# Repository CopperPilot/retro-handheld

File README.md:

# CopperPilot Retro Handheld

**A vertical pocket game console, 63 x 81 x 17 mm, in a CNC-machined metal case: STM32F412 microcontroller, 2.4-inch 320x240 IPS screen, D-pad, ABXY, Start/Select and four shoulder buttons, a 1200 mAh LiPo and USB-C charging. Designed end to end by CopperPilot from four photos and a two-line prompt.**

> [!NOTE]
> **Designed by [CopperPilot](https://copperpilot.ai).** CopperPilot's agents designed every board, schematic, layout and enclosure part in this repo from one prompt and a few reference photos, then checked them with the gates and reviews below. Nobody edited the design files by hand. The whole prompt was two lines ("Build me a handheld retro game console like the one in these photos. It should run simple 2D games and charge over USB-C."); the agents chose the parts, drew and routed the board, modelled the case and fixed every review finding themselves. **It has not been fabricated, assembled or powered on yet.** Everything here is open for review: if you see something a senior engineer would flag, [open an issue](../../issues/new/choose).

One two-layer board fills the case behind the screen. It carries the STM32F412 microcontroller, the button matrix
(surface-mount tact switches under the D-pad, face and shoulder buttons), the display's 18-pin ZIF connector, the
USB-C port and the battery charger. The LiPo pack sits behind the board; the CNC case is a front and a rear shell
with machined button caps and a display window.

## Status

### Done

- [x] Schematic: KiCad ERC, 0 errors
- [x] Layout: KiCad DRC with schematic parity and zone refill, 0 errors, 0 unconnected
- [x] Board rules no looser than the fab's limits, nothing silenced
- [x] Every part on the footprint and 3D model of its exact LCSC part
- [x] Every placed part has a live, in-stock LCSC/JLCPCB part number
- [x] High-speed groups (USB, MIPI, DDR where present) routed, length-matched, on target impedance
- [x] Every user-facing connector opens towards its case opening (checked on its 3D model)
- [x] Every connector mates from a known side, with a keep-clear zone KiCad DRC enforces
- [x] Both ends of every board-to-board cable carry the same signal on each wire
- [x] Datasheet-level design review: 0 P0 and 0 P1 findings open on every board
- [x] Enclosure parts are closed solids that fit the product envelope
- [x] Every enclosure part is manufacturable by its process (wall thickness, build size)
- [x] Full assembly with the real PCBAs: no collisions, seated or along any insertion path
- [x] Every cable joins two real connectors and fits its route in every pose
- [x] Every connector faces what mates with it; every screw hole sits on a boss
- [x] Every port opening has its connector right behind it
- [x] Every button and control physically reaches the switch it works
- [x] Every part is held by something real (screw, snap, clip, adhesive, press fit)
- [x] Gerbers, drill, BOM and CPL exist and agree with the PCB
- [x] Independent judge (compares renders to the reference photos): **9/10** ([notes](reviews/judge.md))

### Pending

- [ ] Gate `sourcing.bom` warn: 18 extended parts (each adds a JLCPCB feeder fee); prefer basic parts where equivalent
- [ ] Gate `kicad.drc` warn: DRC warning silk_over_copper x84
- [ ] **Not built.** The board has not been fabricated or assembled and the case has not been machined.
- [ ] **No firmware.** The game runtime, display driver, button scanning and battery monitoring for the STM32 are not written or tested.
- [ ] **Bought parts are specified from drawings.** The display module and the battery pack are modelled from their published drawings; the exact supplier parts still have to be confirmed against those models.
- [ ] **Thermal and battery life not measured.** No runtime estimate has been checked on hardware.

0 P0 · 0 P1 · 0 P2 review findings open; the full reviews with evidence and suggested fixes are in [reviews/](reviews). Every P0 and P1 the reviews raised was fixed before release.

## Build film

[docs/build-film.mp4](docs/build-film.mp4) (48 s, 720p). Every part backs out along the direction it was fitted and goes back in assembly order, and every cable is drawn along its real route. Every frame is replayed against the 3D models (no part passes through another, the camera stays outside, the product stays in frame and faces you, no flicker), and a separate critic watches the film ([notes](reviews/film.md)).

## Renders

| | |
|:---:|:---:|
| <br>*Three-quarter view* | <br>*Front* |
| <br>*Rear* | <br>*Exploded* |
| <br>*Inside, top cover lifted away, every cable* | <br>*Inside from below, bottom cover lifted away* |
| <br>*Ports* | <br>*Buttons and controls, next to the parts they press* |

## What's inside

**Power path:** USB-C (5 V, ESD-protected) → TP4056 linear charger → 1S 1200 mAh LiPo (pack with its own protection
board) → P-FET/Schottky power path → RT6150 buck-boost to a steady 3.3 V across the whole battery range.
**Display:** 2.4-inch 320x240 IPS module (ILI9341 class) over SPI on a 0.5 mm FPC, backlight switched by a MOSFET.

| Board | Size | Layers | Parts | Tracks | Vias | KiCad project | Review |
|---|---|---|---|---|---|---|---|
| Main board | 58 × 76 mm | 2 | 140 | 3,190 | 241 | [`hardware/pocket-retro-handheld.kicad_pro`](hardware/pocket-retro-handheld.kicad_pro) | [0 P0 · 0 P1](reviews/review-main.md) |

**Bought parts** (modelled from their drawings; the assembly checks use these models):

- **Display**: 2.4-inch 4:3 320x240 IPS TFT LCD module
- **Battery**: 1S 3.7V 1200mAh 503450 Li-Polymer rechargeable battery pack with built-in PCM protection and 2-pin 1.25mm Molex PicoBlade lead

## How it was made

CopperPilot's agents worked from the prompt in [reference/prompt.md](reference/prompt.md) and 4 reference photos ([reference/](reference)). The pipeline scopes the product into a written contract ([design/spec.yaml](design/spec.yaml)), designs the boards and the enclosure in parallel, integrates them, and only moves on when the gates pass. A separate review agent reads every board against the part datasheets, and a separate judge compares the result with the photos.

- Pipeline wall clock: about **19 h** over 9 launches (pipeline v98 to v127).

**Reference vs build:**

<sub>Reference photos of a commercial product, used here only for comparison. All rights belong to their owners; this project is not affiliated with or endorsed by the product's maker.</sub>

## Repository layout

```
hardware/          KiCad 10 projects (main board at the top, daughter boards in their own folders)
  lcsc.*, rea_refs.*   symbols, footprints and 3D models for every part, so the project opens anywhere
case/out/          enclosure parts (STL)
case/purchased/    bought parts used in the assembly checks
case/generate_case.py  the parametric enclosure source (uses CopperPilot's CAD helpers, not yet public)
fab/               Gerbers, drill, BOM, CPL, schematic PDF and STEP for each board; fab/mech/ enclosure STEP/STL
design/spec.yaml   the design contract the agents wrote and the gates check
reviews/           gate report, design reviews, the judge's notes, KiCad ERC/DRC
reference/         the prompt and the reference photos
docs/              build film and renders
```

## Manufacture

Every board targets **JLCPCB** standard PCB + assembly (1.6 mm FR-4); every part has an LCSC number. Per board: upload `*-gerbers.zip`, then `*-bom.csv` and `*-cpl.csv` for assembly, and check the part rotations in JLCPCB's preview before ordering.

The case (`fab/mech/`) is designed for CNC-machined 6061 aluminium (anodised); STEP files are included for machining
quotes and STLs for test prints.

> [!WARNING]
> This design has not been built yet. Fix or accept the open review findings above before you order boards, and expect a first revision to need changes.

## Review this design

Hardware gets better with more eyes on it. We'd like to hear what you'd flag:

- **Open an issue** ([design review template](../../issues/new/choose)) for a wrong pin, a missing part, a tight clearance, a part you'd swap, or a P1 above you disagree with.
- **Send a pull request** with a fix. Say which board and which reference designators it touches.
- **Build one** and tell us how it went: photos, bring-up notes and failures are all welcome.

Start with [reviews/](reviews): every finding has its evidence and a suggested fix.

## License

[CERN-OHL-S-2.0](LICENSE). You may use, study, modify, make and sell products from this design; modified versions must be shared under the same licence.

Part and product names are used only to say what fits; all trademarks belong to their owners.

<p align="center"><a href="https://copperpilot.ai"><b>Designed by CopperPilot</b></a>: we accelerate hardware design.<br><sub>More open designs: <a href="https://github.com/CopperPilot">github.com/CopperPilot</a></sub></p>

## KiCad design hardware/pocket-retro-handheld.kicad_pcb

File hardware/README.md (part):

# Pocket Retro Game Console — Hardware Design & Verification

Generated from `rea/spec.yaml` and completed with verified JLCPCB/LCSC components (`hardware/lcsc.kicad_sym`, `hardware/lcsc.pretty`, `hardware/lcsc.3dshapes`).

## 1. Architecture & Block Summary
- **MCU, Clock, VCAP_1 & VDDA Conditioning, External Button-Chord DFU Override, Bootloader Idle Conditioning & SWD Breakout (`U1`, `Y1`, `C1`, `C2`, `C10`, `L2`, `C21`, `C22`, `Q12`, `Q13`, `Q14`, `SW15`, `SW16`, `R25..R29`, `TP1..TP6`):**
  - `STM32F412RET6` (`U1`, LCSC `C89374`, LQFP-64): 100 MHz ARM Cortex-M4F (operated at `SYSCLK = 80 MHz` / `APB2 = 80 MHz`) with 512 KB Flash and 256 KB contiguous DMA-capable SRAM.
  - 12 MHz Low-$C_L$, Low-ESR HSE Crystal (`Y1`, `TXM12M0004322CBCDO00T`, LCSC `C362368`, SMD3225-4P): $C_L = 9\text{ pF}$, $\text{ESR}_{\max} = 60\ \Omega$, $C_0 \approx 3\text{ pF}$. Critical transconductance $g_{m,\text{crit}} = 4 \times 60\ \Omega \times (2\pi \times 12\text{ MHz})^2 \times (9\text{ pF} + 3\text{ pF})^2 \approx 0.20\text{–}0.25\text{ mA/V} \ll G_{m,\text{crit,max}} = 1.0\text{ mA/V}$ (gain margin $> 16$, compliant with ST AN2867 and STM32F412xE DS11189 Section 6.3.9). Load capacitors `C1 = C2 = 12 pF` 50 V C0G (`0402CG120J500NT`, LCSC `C1547`) provide $C_{L,\text{actual}} = (12 \times 12)/(12 + 12) + C_{\text{stray}}(3\text{ pF}) = 6\text{ pF} + 3\text{ pF} = 9.0\text{ pF}$.
  - Single-`VCAP_1` Core LDO Decoupling (`U1.30`): Because LQFP-64 bonds out a single internal core voltage regulator capacitor pin (`VCAP_1`, `U1.30`), `VCAP_1` is decoupled by a 4.7 uF 16 V 0603 X5R low-ESR ($\ll 1\ \Omega$) ceramic capacitor `C10` (`CL10A475KO8NNNC`, LCSC `C19666`), meeting ST DS11189 Table 21 and AN4488 ($1 \times 4.7\ \mu\text{F}$ nominal for single-VCAP packages).
  - Analog Supply Isolation (`U1.13` `VDDA/VREF+`): Isolated from digital `+3V3` via 0603 ferrite bead `L2` (`BLM18PG121SN1D`, LCSC `C14709`, $120\ \Omega$ @ 100 MHz, $R_{\text{DC}} = 50\text{ m}\Omega$, 2 A) feeding net `VDDA`, locally decoupled adjacent to `U1.13` (`VDDA`) and `U1.12` (`VSSA`) by `C21` = 100 nF (`CL05B104KB54PNC`, LCSC `C307331`) and `C22` = 1 uF (`CL05A105KO5NNNC`, LCSC `C29266`).
  - Factory-ROM USB DFU, External Button-Chord Recovery (`Select + R2 + B`), Reset & SWD Programming:
    - `BOOT0` (`U1.60`) has a 10 kOhm pull-down to `GND` (`R8`, LCSC `C25744`) for normal Flash boot (`BOOT1`/`PB2` pulled low via 10 kOhm `R11`).
    - For bare-PCBA bring-up prior to LCD installation, tactile switch `SW15` (`B3U-1000P`, LCSC `C231329`) and test pad `TP6` pull `BOOT0` to `+3V3`, tactile switch `SW16` (`B3U-1000P`) and `TP3` pull `NRST` (`U1.7`, with 10 kOhm pull-up `R7` and 100 nF filter `C8`) low, and `TP1..TP6` (`RH-5015`, LCSC `C5199798`) expose `SWDIO` (`PA13`), `SWCLK` (`PA14`), `NRST`, `+3V3`, `GND`, and `BOOT0`.
    - For sealed-enclosure recovery without opening the press-fit CNC shell, series P-MOSFETs `Q12` (`AO3401A`, Source on `+3V3`, Gate on `BTN_SELECT`, Drain on `BOOT0_CHORD_MID`) and `Q13` (`AO3401A`, Source on `BOOT0_CHORD_MID`, Gate on `BTN_R2`, Drain on `BOOT0`) pull `BOOT0` to `+3V3` (`3.30 V` across `R8 = 10 kOhm`) whenever external buttons `Select` (`SW9`) and `R2` (`SW13`) are held simultaneously. While `BOOT0 = 3.30 V` biases the gate of N-MOSFET `Q14` (`AO3400A`, Gate on `BOOT0`, Source on `BTN_B`, Drain on `NRST`), pressing and releasing external button `B` (`SW8`) pulls `NRST` low through `Q14` ($V_{\text{GS}} = 3.30\text{ V}$) and releases `NRST` with `BOOT0 = 1`, cleanly entering the ST System Memory ROM USB DFU bootloader from outside the enclosure. During normal gameplay (`BOOT0 = 0 V`), `Q14` has $V_{\text{GS}} = 0\text{ V}$ and its internal body diode (anode on `BTN_B`, cathode on `NRST`) is reverse-biased when `BTN_B` is pressed.
    - Dedicated 10 kOhm pull-ups to `+3V3` (`R25..R29`, plus `R14`/`R15` and button pull-ups `R33..R45`, `R19`) hold all active AN2606 system-memory bootloader pins idle high during DFU enumeration.
- **USB-C Power, CC1/CC2 ADC Current-Advertisement Sensing, Controlled TP4056 Charging & 0V Battery Wake / Reverse-Polarity Protection (`J1`, `F1`, `C3`, `D3`, `D4`, `U4`, `R1`, `R2`, `R52`, `R53`, `U2`, `R3`, `R51`, `F2`, `Q6`, `Q7`, `Q11`, `R20`, `R30`, `R31`, `Q1`, `D1`, `J3`, `R23`, `R24`):**
  - 16-pin USB-C receptacle `J1` (`TYPE-C-31-M-12`, LCSC `C165948`) configured as an autonomous 5 V sink with independent 5.1 kOhm Rd pull-down resistors (`R1`, `R2`, LCSC `C25905`) on `CC1` (`A5`) and `CC2` (`B5`), protected against ESD and overvoltage transients by a 5 V low-clamping bidirectional dual TVS diode `D4` (`PESD5V0S2BT`, LCSC `C2687130`, $V_{\text{RWM}} = 5.0\text{ V}$, $V_{\text{BR}} = 6.0\text{–}7.2\text{ V}$, $V_{\text{CL}} = 9\text{ V}$ typ at $I_{\text{PP}} = 1\text{ A}$, $12\text{ V}$ max at $I_{\text{PP}} = 3\text{ A}$).
  - USB-C Source Current Advertisement Sensing (`USB_CC1_ADC` on `U1.14` `PA0`/`ADC1_IN0`, `USB_CC2_ADC` on `U1.27` `PB1`/`ADC1_IN9`): `USB_CC1` and `USB_CC2` are routed through 10 kOhm 1% 0402 series current-limiting resistors `R52` and `R53` (`0402WGF1002TCE`, LCSC `C25744`) to `U1.14` (`PA0`/`ADC1_IN0`) and `U1.27` (`PB1`/`ADC1_IN9`). The total external ADC source impedance is $R_{\text{AIN}} = 5.1\text{ k}\Omega + 10\text{ k}\Omega = 15.1\text{ k}\Omega \le 50\text{ k}\Omega$ ($R_{\text{AIN,max}}$ per STM32F412 DS11189 Table 65), while `D4` (`PESD5V0S2BT`) + `R52`/`R53` (`10 kOhm`) limit pin injection current during any ESD/overvoltage event to $\le (12\text{ V} - 0\text{ V}) / 10\text{ k}\Omega = 1.2\text{ mA} \ll 5.0\text{ mA}$ ($|I_{\text{INJ(PIN)}}|$ rating in DS11189 Table 14), safely measuring the voltage across `R1` and `R2` to detect Default USB power ($0.25\text{–}0.61\text{ V}$, $0.41\text{ V}$ typ), 1.5 A Type-C source advertisement ($0.70\text{–}1.16\text{ V}$, $0.92\text{ V}$ typ), or 3.0 A Type-C source advertisement ($1.31\text{–}2.04\text{ V}$, $1.68\text{ V}$ typ).
  - Controlled `TP4056` (`U2`, LCSC `C725790`) Charger Enable & USB 2.0 Current Compliance (`U2.8` `CE` on `CHG_CE`, `U1.54` `PD2`, `R51`, `R3`):
    - `U2.8` (`CE`) is connected to `U1.54` (`PD2`) on net `CHG_CE` with a 100 kOhm pull-down resistor `R51` (`0402WGF1003TCE`, LCSC `C25741`) to `GND`. Upon USB plug-in, during reset, or prior to USB enumeration, `R51` holds `CHG_CE = 0 V` ($< 0.8\text{ V}$ `TP4056` shutdown threshold), keeping `U2` disabled ($I_{\text{CC}} \le 55\ \mu\text{A}$) while backlight MOSFET `Q2` is held off by `R10` = 100 kOhm. Total unconfigured `/VBUS` current is therefore only the `U3` + `U1` startup current ($\sim 40.6\text{ mA} \le 100\text{ mA}$ USB 2.0 unconfigured limit).
    - `R3` (`0402WGF3301TCE`, LCSC `C25890`, 3.3 kOhm 1%) programs `U2` charge current to $I_{\text{CHG}} = 1200\text{ V} / 3.3\text{ k}\Omega = 363.6\text{ mA}$ ($0.30\text{C}$ for the 1200 mAh cell, $P_{\text{diss,max}} \le 0.71\text{ W}$). Once USB enumeration completes (or 1.5 A / 3.0 A Type-C advertisement is detected on `PA0`/`PB1`), `U1` drives `PD2 = HIGH` (`3.30 V > 1.5 V` `TP4056` enable threshold). During simultaneous play-while-charging at 100% backlight duty cycle, total `/VBUS` current is $363.6\text{ mA (U2)} + 40.6\text{ mA (U3)} + 64.0\text{ mA (J2)} = 468.2\text{ mA}$ typ ($480.2\text{ mA}$ max at $V_{\text{BUS}} = 5.25\text{ V}$), strictly within the **500 mA USB 2.0 SDP limit**.
  - 0V PCM-Tripped Battery Wake & Reverse-Polarity Protection (`J3`, `F2`, `Q6`, `Q7`, `Q11`, `R20`, `R30`, `R31`):
    - Battery connector `J3` (Molex PicoBlade `53261-0271`, LCSC `C177225`) is protected immediately adjacent to `J3` by series PTC polyfuse `F2` (`BSMD0805-110-12V`, LCSC `C910824`) and P-MOSFET `Q6` (`AO3401A`, LCSC `C15127`, Source on `VBAT`, Drain on `VBAT_FUSED`, Gate on `VBAT_RP_G` with 100 kOhm source-gate pull-up `R20` `C25741` and pull-down N-MOSFET `Q7` `AO3400A` `C20917`).
    - `Q7` Gate (`VBAT_RP_EN`) is biased from `VSYS` through `R31` = 100 kOhm (`0402WGF1003TCE`, LCSC `C25741`) and clamped to `VBAT_FUSED` through `R30` = 10 kOhm (`0402WGF1002TCE`, LCSC `C25744`) in series with negative-polarity clamp N-MOSFET `Q11` (`AO3400A`, LCSC `C20917`, Gate on `GND`, Source on `VBAT_FUSED`, Drain on `VBAT_RP_CLAMP`):
      1. **0V PCM-Tripped Pack + USB Connected (`VBAT_FUSED = 0 V`, `VSYS = 4.70 V`):** `Q11` has $V_{\text{GS}} = 0\text{ V}$ (channel off) and its internal body diode (anode on `VBAT_FUSED`, cathode on `VBAT_RP_CLAMP`) is reverse-biased. `R31` pulls `VBAT_RP_EN` to `VSYS = 4.70 V`, turning `Q7` and `Q6` on so `U2` (`TP4056`) can deliver its $36.4\text{ mA}$ trickle-charge current into `J3.1` to reset the battery PCM and wake the pack.
      2. **Battery-Only Normal Operation (`VBAT_FUSED = +2.5 V..+4.2 V`, `VBUS = 0 V`):** `Q11`'s body diode conducts forward through `R30 = 10 kOhm` and `R31 = 100 kOhm` pulls from `VSYS`, biasing `VBAT_RP_EN` to $+2.5\text{–}4.2\text{ V}$ and keeping `Q7` and `Q6` fully enhanced ($V_{\text{GS}}(Q_6) = -V_{\text{BAT}}$).
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
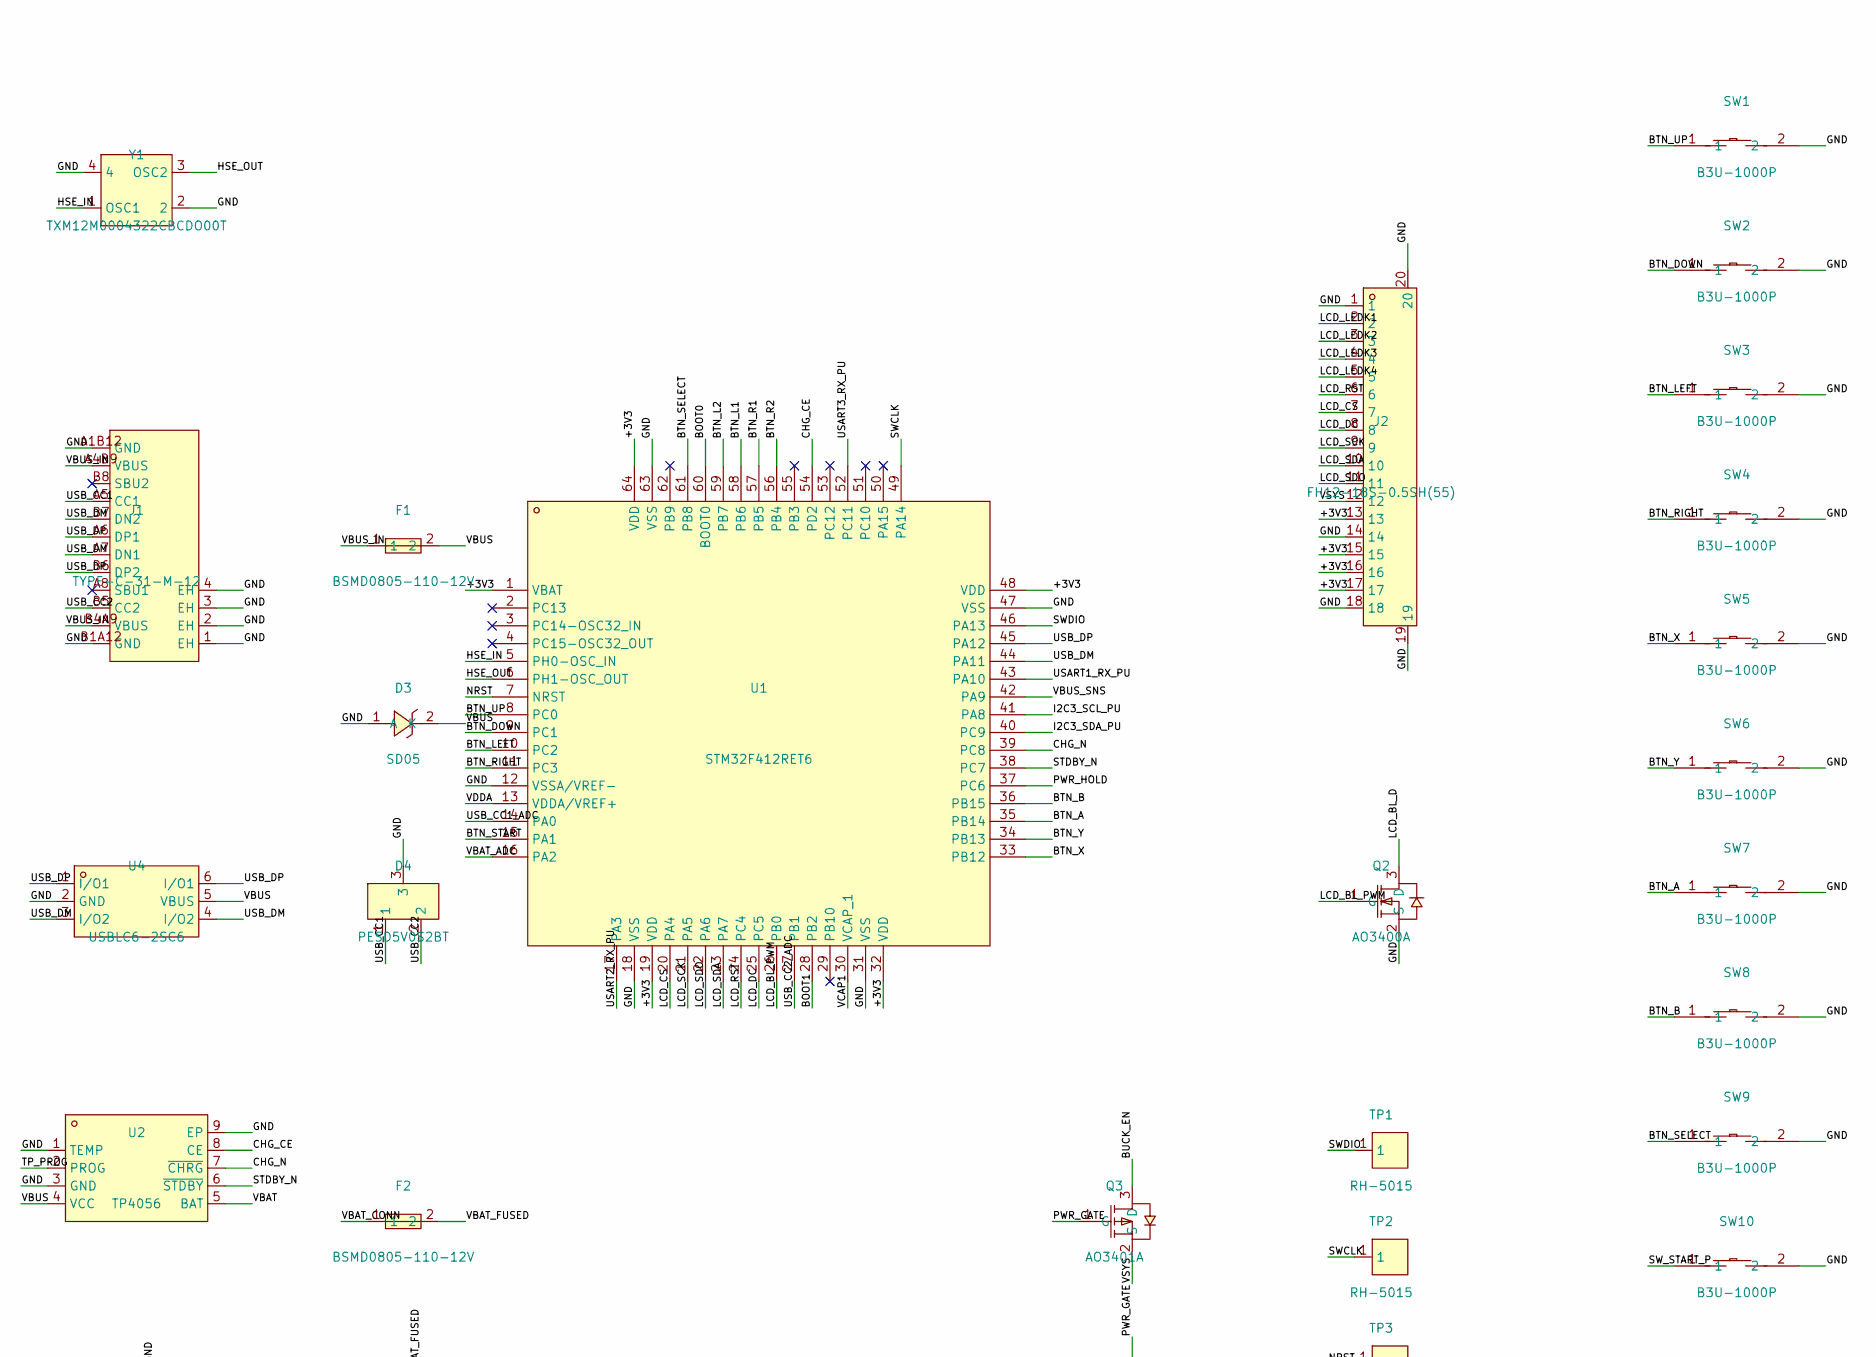
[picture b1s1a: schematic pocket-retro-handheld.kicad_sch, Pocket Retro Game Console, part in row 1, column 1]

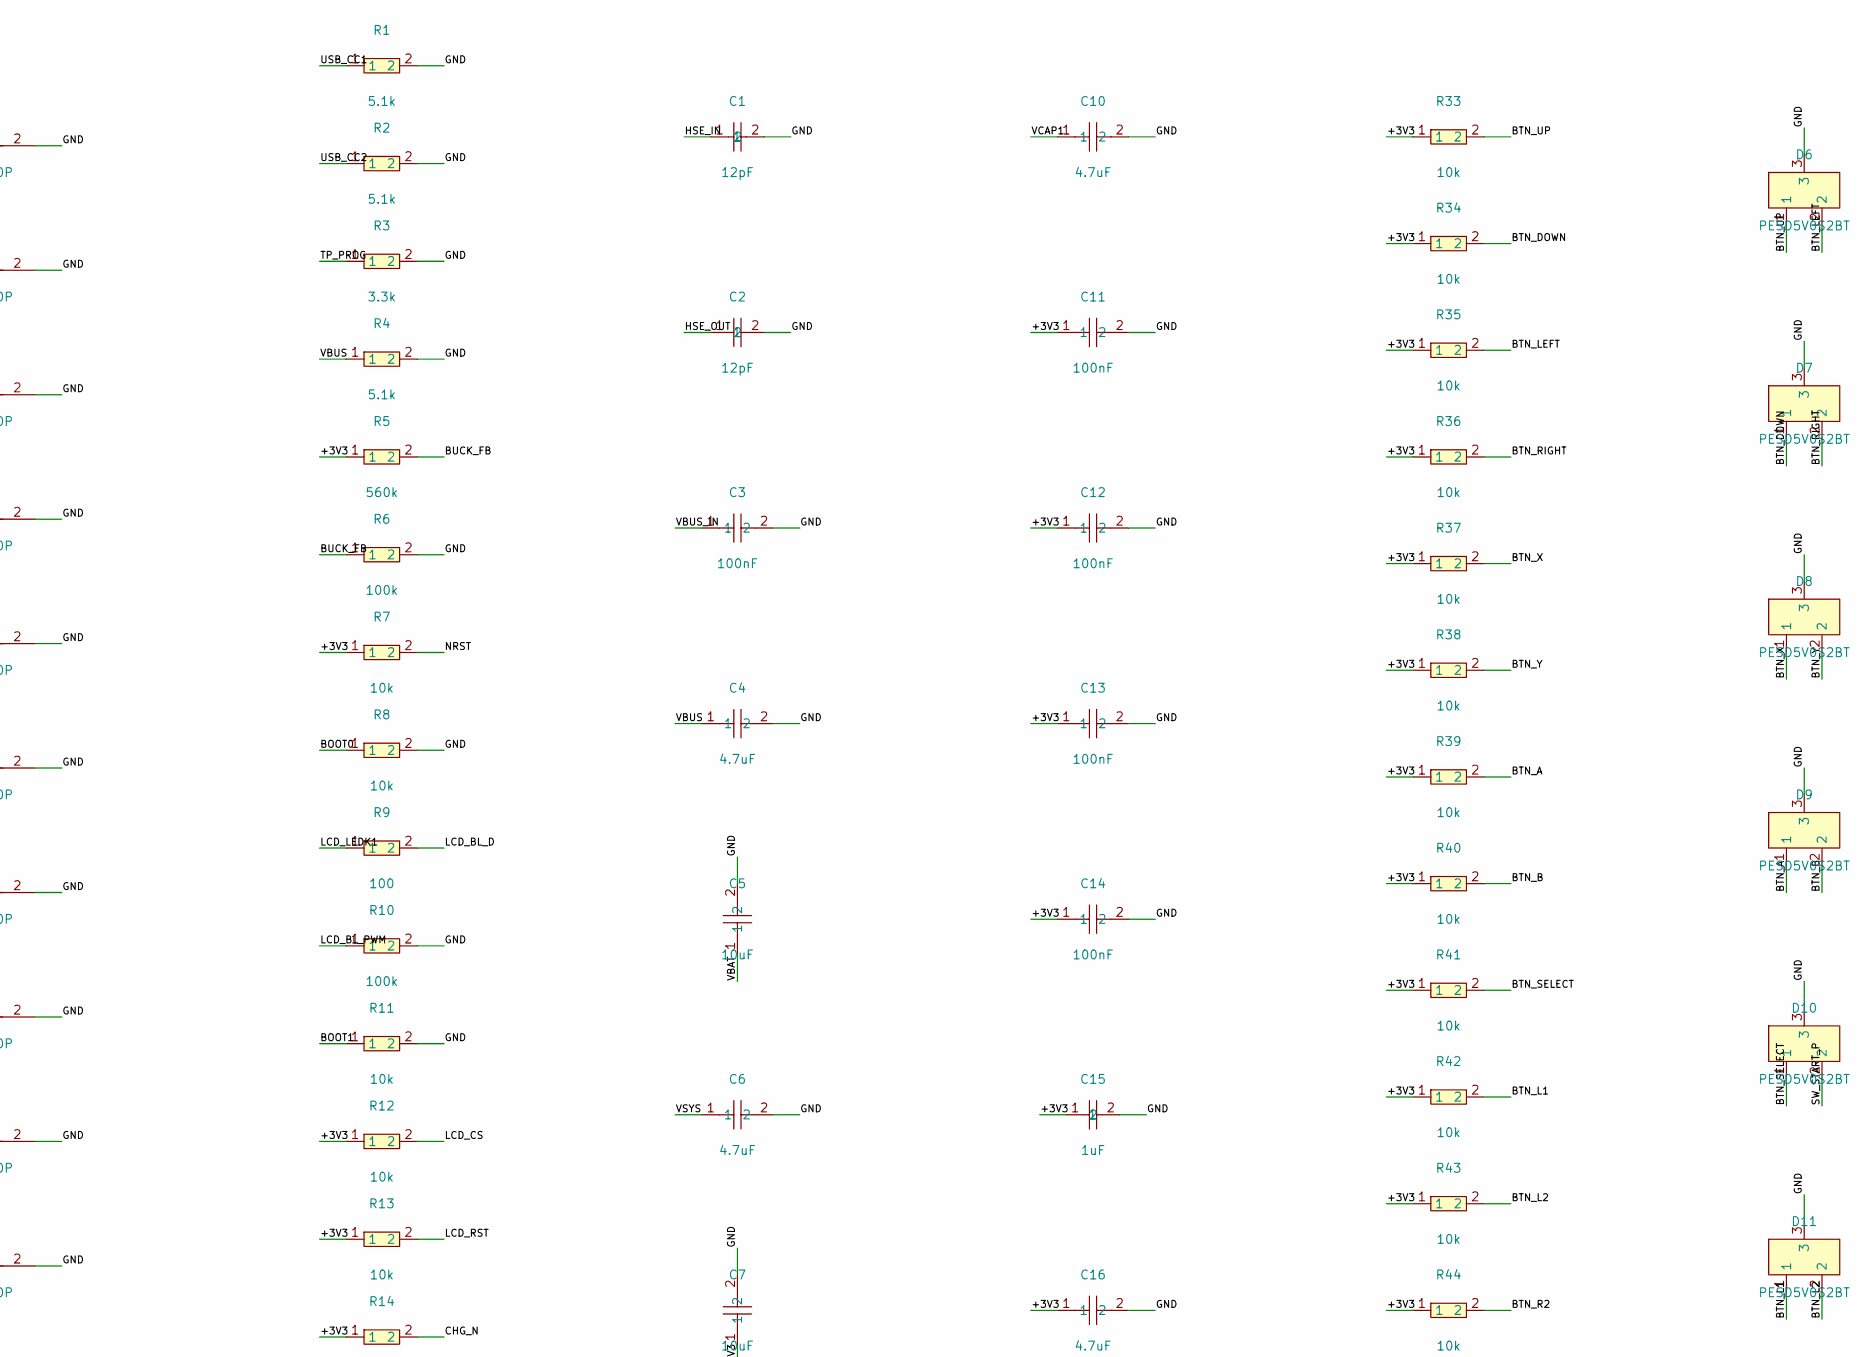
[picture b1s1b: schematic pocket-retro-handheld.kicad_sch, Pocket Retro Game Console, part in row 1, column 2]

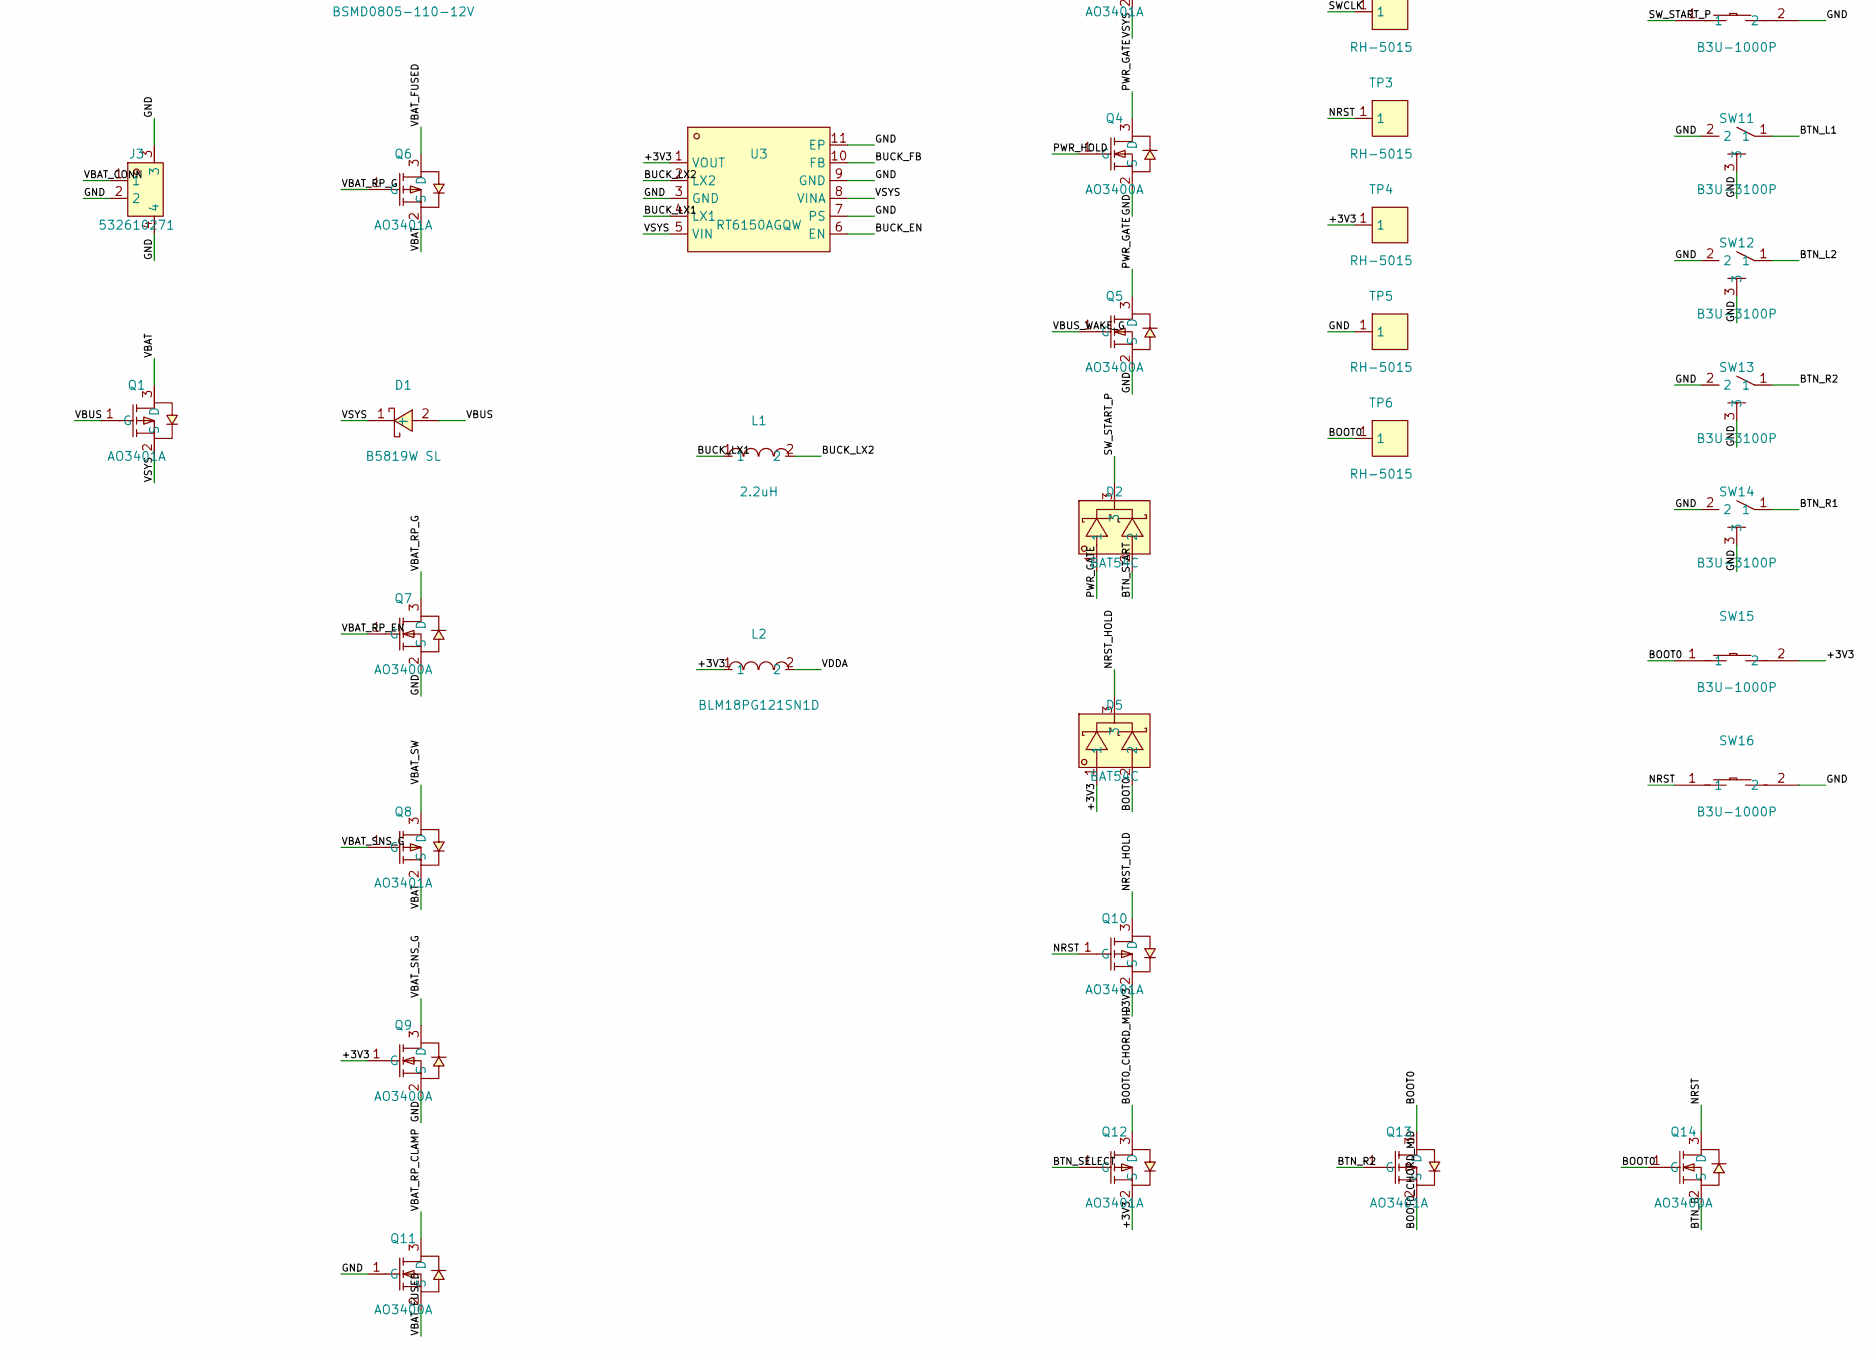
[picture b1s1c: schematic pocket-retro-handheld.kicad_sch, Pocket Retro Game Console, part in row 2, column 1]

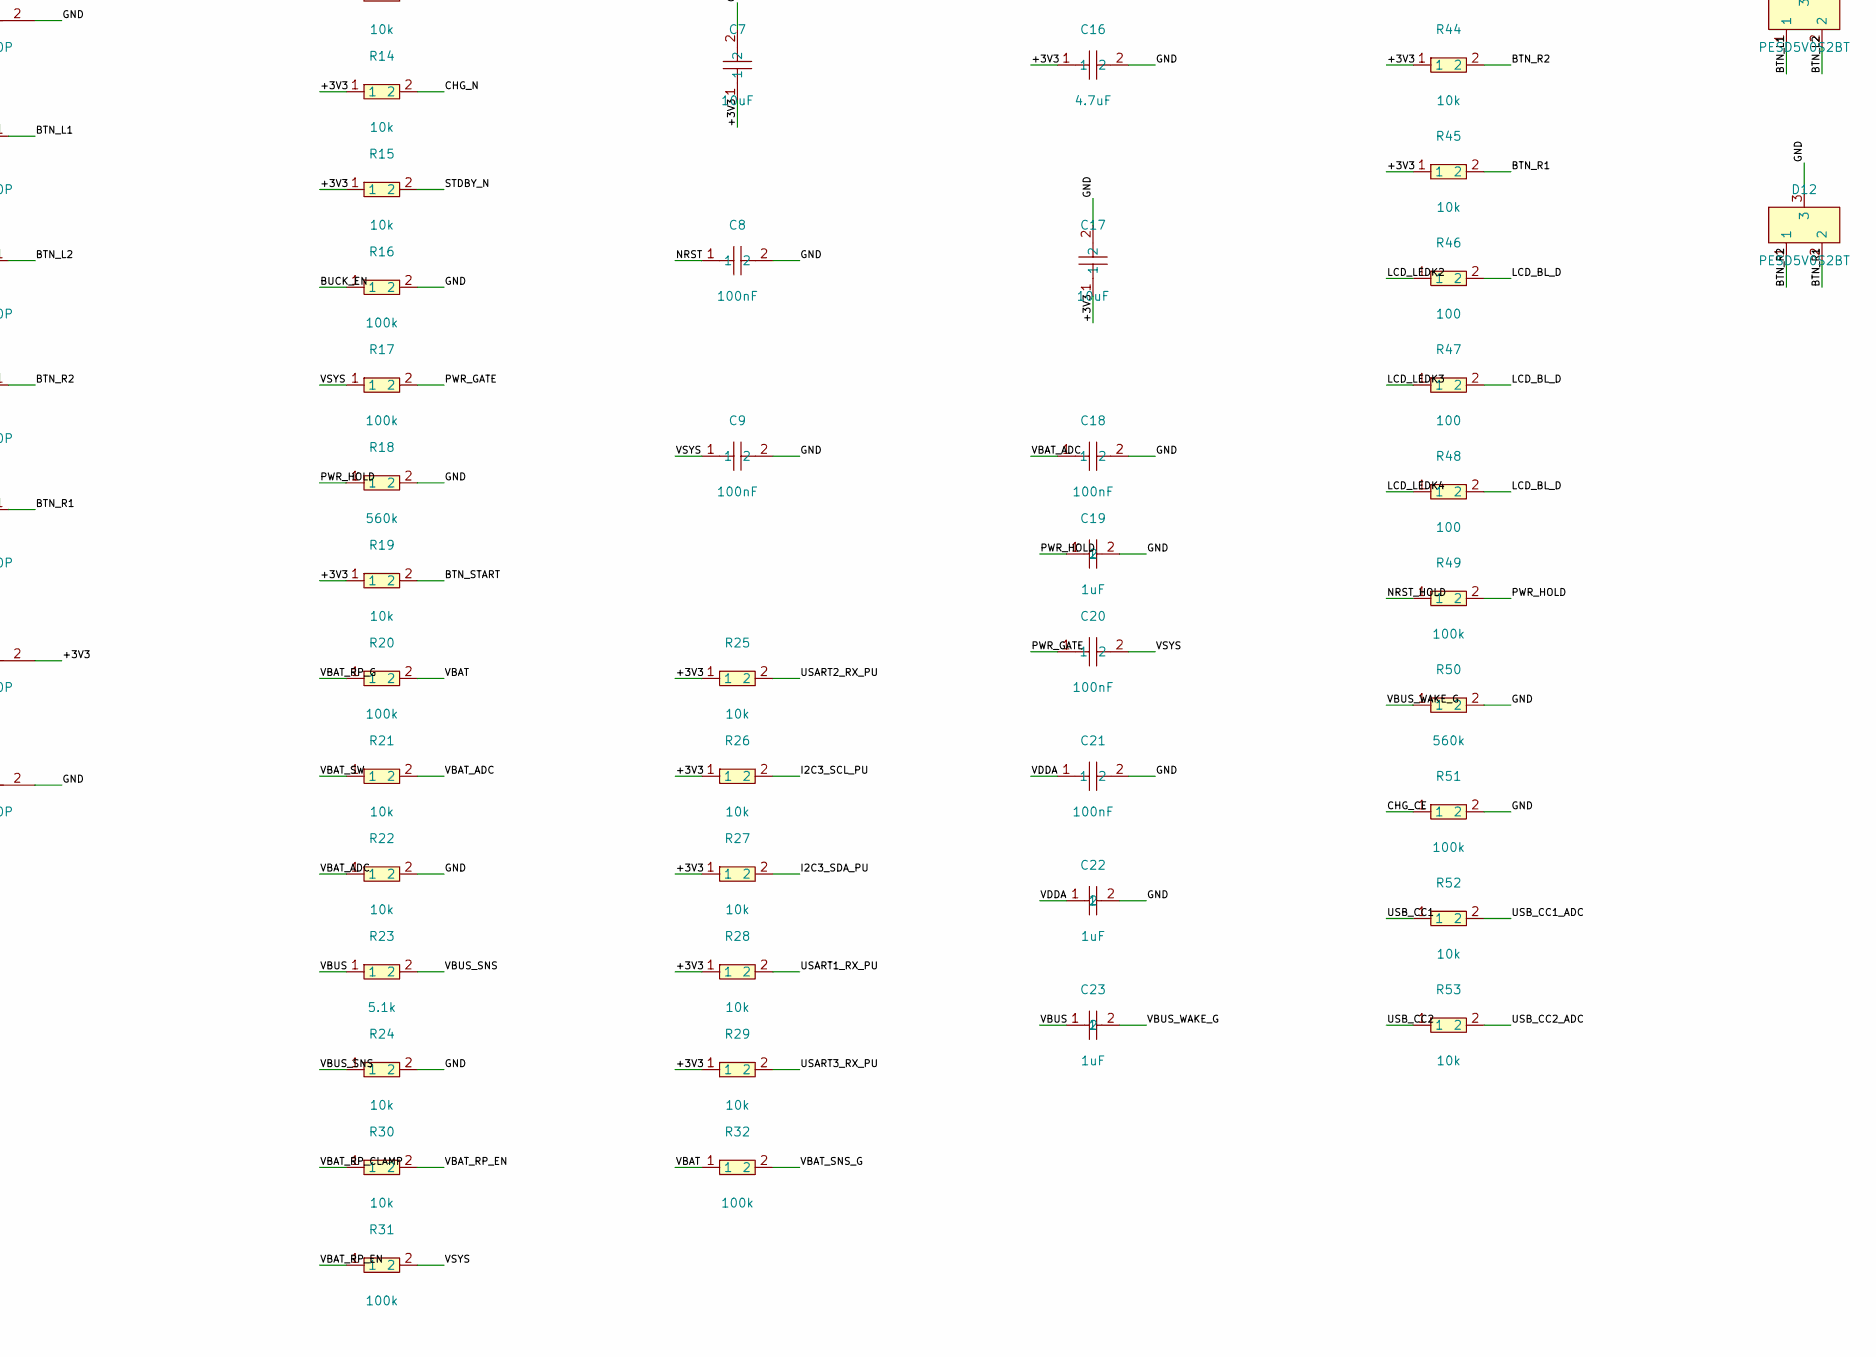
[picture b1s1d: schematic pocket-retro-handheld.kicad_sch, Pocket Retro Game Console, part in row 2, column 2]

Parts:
C1, C2: 12pF; C0402; MPN 0402CG120J500NT; LCSC C1547
C3, C8, C9, C11, C12, C13, C14, C18, C20, C21: 100nF; C0402; MPN CL05B104KB54PNC; LCSC C307331
C4, C6, C10, C16: 4.7uF; C0603; MPN CL10A475KO8NNNC; LCSC C19666
C5, C7, C17: 10uF; C0603; MPN TCC0603X5R106M160CT; LCSC C380317
C15, C19, C22, C23: 1uF; C0402; MPN CL05A105KO5NNNC; LCSC C29266
D1: B5819W SL; SOD-123_L2.7-W1.6-LS3.7-RD-1; MPN B5819W SL; LCSC C8598
D2, D5: BAT54C; SOT-23-3_L2.9-W1.3-P1.90-LS2.4-BR; MPN BAT54C; LCSC C916424
D3: SD05; SOD-323_L1.8-W1.3-LS2.5-FD; MPN SD05; LCSC C502527
D4, D6, D7, D8, D9, D10, D11, D12: PESD5V0S2BT; SOT-23-3_L2.9-W1.3-P0.95-LS2.4-BR; MPN PESD5V0S2BT; LCSC C2687130
F1, F2: BSMD0805-110-12V; F0805; MPN BSMD0805-110-12V; LCSC C910824
J1: TYPE-C-31-M-12; USB-C_SMD-TYPE-C-31-M-12_1; MPN TYPE-C-31-M-12; LCSC C165948
J2: FH12-18S-0.5SH(55); FPC-SMD_FH12-18S-0.5SH-55; MPN FH12-18S-0.5SH(55); LCSC C506792
J3: 532610271; CONN-SMD_532610271; MPN 532610271; LCSC C177225
L1: 2.2uH; IND-SMD_L3.0-W3.0; MPN SWPA3015S2R2MT; LCSC C43389
L2: BLM18PG121SN1D; L0603; MPN BLM18PG121SN1D; LCSC C14709
Q1, Q3, Q6, Q8, Q10, Q12, Q13: AO3401A; SOT-23_L2.9-W1.3-P1.90-LS2.4-BR; MPN AO3401A; LCSC C15127
Q2, Q4, Q5, Q7, Q9, Q11, Q14: AO3400A; SOT-23-3_L2.9-W1.3-P1.90-LS2.4-BR; MPN AO3400A; LCSC C20917
R1, R2, R4, R23: 5.1k; R0402; MPN 0402WGF5101TCE; LCSC C25905
R3: 3.3k; R0402; MPN 0402WGF3301TCE; LCSC C25890
R5, R18, R50: 560k; R0402; MPN 0402WGF5603TCE; LCSC C132339
R6, R10, R16, R17, R20, R31, R32, R49, R51: 100k; R0402; MPN 0402WGF1003TCE; LCSC C25741
R7, R8, R11, R12, R13, R14, R15, R19, R21, R22, R24, R25, R26, R27, R28, R29, R30, R33, R34, R35, R36, R37, R38, R39, R40, R41, R42, R43, R44, R45, R52, R53: 10k; R0402; MPN 0402WGF1002TCE; LCSC C25744
R9, R46, R47, R48: 100; R0603; MPN 0603WAF1000T5E; LCSC C22775
SW1, SW2, SW3, SW4, SW5, SW6, SW7, SW8, SW9, SW10, SW15, SW16: B3U-1000P; KEY-SMD_B3U-1000PM; MPN B3U-1000P; LCSC C231329
SW11, SW12, SW13, SW14: B3U-3100P; SW-SMD_3P-L3.0-W2.5-LS4.0; MPN B3U-3100P; LCSC C6748648
TP1, TP2, TP3, TP4, TP5, TP6: RH-5015; SMD_RH-5015; MPN RH-5015; LCSC C5199798
U1: STM32F412RET6; LQFP-64_L10.0-W10.0-P0.50-LS12.0-BL; MPN STM32F412RET6; LCSC C89374
U2: TP4056; ESOP-8_L4.9-W3.9-P1.27-LS6.0-BL-EP; MPN TP4056; LCSC C725790
U3: RT6150AGQW; WDFN-10_L3.0-W3.0-P0.50-BL-EP; MPN RT6150AGQW; LCSC C147971
U4: USBLC6-2SC6; SOT-23-6_L2.9-W1.6-P0.95-LS2.8-BL; MPN USBLC6-2SC6; LCSC C2687116
Y1: TXM12M0004322CBCDO00T; OSC-SMD_4P-L3.2-W2.5-BL; MPN TXM12M0004322CBCDO00T; LCSC C362368

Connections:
/+3V3: C7.1, C11.1, C12.1, C13.1, C14.1, C15.1, C16.1, C17.1, D5.1, J2.13, J2.15, J2.16, J2.17, L2.1, Q9.1 (G), Q10.2 (S), Q12.2 (S), R5.1, R7.1, R12.1, R13.1, R14.1, R15.1, R19.1, R25.1, R26.1, R27.1, R28.1, R29.1, R33.1, R34.1, R35.1, R36.1, R37.1, R38.1, R39.1, R40.1, R41.1, R42.1, R43.1, R44.1, R45.1, SW15.2, TP4.1, U1.1 (VBAT), U1.19 (VDD), U1.32 (VDD), U1.48 (VDD), U1.64 (VDD), U3.1 (VOUT)
/BOOT0: D5.2, Q13.3 (D), Q14.1 (G), R8.1, SW15.1, TP6.1, U1.60 (BOOT0)
/BOOT0_CHORD_MID: Q12.3 (D), Q13.2 (S)
/BOOT1: R11.1, U1.28 (PB2)
/BTN_A: D9.1, R39.2, SW7.1, U1.35 (PB14)
/BTN_B: D9.2, Q14.2 (S), R40.2, SW8.1, U1.36 (PB15)
/BTN_DOWN: D7.1, R34.2, SW2.1, U1.9 (PC1)
/BTN_L1: D11.1, R42.2, SW11.1, U1.58 (PB6)
/BTN_L2: D11.2, R43.2, SW12.1, U1.59 (PB7)
/BTN_LEFT: D6.2, R35.2, SW3.1, U1.10 (PC2)
/BTN_R1: D12.2, R45.2, SW14.1, U1.57 (PB5)
/BTN_R2: D12.1, Q13.1 (G), R44.2, SW13.1, U1.56 (PB4)
/BTN_RIGHT: D7.2, R36.2, SW4.1, U1.11 (PC3)
/BTN_SELECT: D10.1, Q12.1 (G), R41.2, SW9.1, U1.61 (PB8)
/BTN_START: D2.2, R19.2, U1.15 (PA1)
/BTN_UP: D6.1, R33.2, SW1.1, U1.8 (PC0)
/BTN_X: D8.1, R37.2, SW5.1, U1.33 (PB12)
/BTN_Y: D8.2, R38.2, SW6.1, U1.34 (PB13)
/BUCK_EN: Q3.3 (D), R16.1, U3.6 (EN)
/BUCK_FB: R5.2, R6.1, U3.10 (FB)
/BUCK_LX1: L1.1, U3.4 (LX1)
/BUCK_LX2: L1.2, U3.2 (LX2)
/CHG_CE: R51.1, U1.54 (PD2), U2.8 (CE)
/CHG_N: R14.2, U1.39 (PC8), U2.7 (~CHRG)
/GND: C1.2, C2.2, C3.2, C4.2, C5.2, C6.2, C7.2, C8.2, C9.2, C10.2, C11.2, C12.2, C13.2, C14.2, C15.2, C16.2, C17.2, C18.2, C19.2, C21.2, C22.2, D3.1 (A), D4.3, D6.3, D7.3, D8.3, D9.3, D10.3, D11.3, D12.3, J1.1 (EH), J1.2 (EH), J1.3 (EH), J1.4 (EH), J1.A1B12 (GND), J1.B1A12 (GND), J2.1, J2.14, J2.18, J2.19, J2.20, J3.2, J3.3, J3.4, Q2.2 (S), Q4.2 (S), Q5.2 (S), Q7.2 (S), Q9.2 (S), Q11.1 (G), R1.2, R2.2, R3.2, R4.2, R6.2, R8.2, R10.2, R11.2, R16.2, R18.2, R22.2, R24.2, R50.2, R51.2, SW1.2, SW2.2, SW3.2, SW4.2, SW5.2, SW6.2, SW7.2, SW8.2, SW9.2, SW10.2, SW11.2, SW11.3, SW12.2, SW12.3, SW13.2, SW13.3, SW14.2, SW14.3, SW16.2, TP5.1, U1.12 (VSSA/VREF-), U1.18 (VSS), U1.31 (VSS), U1.47 (VSS), U1.63 (VSS), U2.1 (TEMP), U2.3 (GND), U2.9 (EP), U3.3 (GND), U3.7 (PS), U3.9 (GND), U3.11 (EP), U4.2 (GND), Y1.2, Y1.4
/HSE_IN: C1.1, U1.5 (PH0-OSC_IN), Y1.1 (OSC1)
/HSE_OUT: C2.1, U1.6 (PH1-OSC_OUT), Y1.3 (OSC2)
/I2C3_SCL_PU: R26.2, U1.41 (PA8)
/I2C3_SDA_PU: R27.2, U1.40 (PC9)
/LCD_BL_D: Q2.3 (D), R9.2, R46.2, R47.2, R48.2
/LCD_BL_PWM: Q2.1 (G), R10.1, U1.26 (PB0)
/LCD_CS: J2.7, R12.2, U1.20 (PA4)
/LCD_DC: J2.8, U1.25 (PC5)
/LCD_LEDK1: J2.2, R9.1
/LCD_LEDK2: J2.3, R46.1
/LCD_LEDK3: J2.4, R47.1
/LCD_LEDK4: J2.5, R48.1
/LCD_RST: J2.6, R13.2, U1.24 (PC4)
/LCD_SCK: J2.9, U1.21 (PA5)
/LCD_SDA: J2.10, U1.23 (PA7)
/LCD_SDO: J2.11, U1.22 (PA6)
/NRST: C8.1, Q10.1 (G), Q14.3 (D), R7.2, SW16.1, TP3.1, U1.7 (NRST)
/NRST_HOLD: D5.3, Q10.3 (D), R49.1
/PWR_GATE: C20.1, D2.1, Q3.1 (G), Q4.3 (D), Q5.3 (D), R17.2
/PWR_HOLD: C19.1, Q4.1 (G), R18.1, R49.2, U1.37 (PC6)
/STDBY_N: R15.2, U1.38 (PC7), U2.6 (~STDBY)
/SWCLK: TP2.1, U1.49 (PA14)
/SWDIO: TP1.1, U1.46 (PA13)
/SW_START_P: D2.3, D10.2, SW10.1
/TP_PROG: R3.1, U2.2 (PROG)
/USART1_RX_PU: R28.2, U1.43 (PA10)
/USART2_RX_PU: R25.2, U1.17 (PA3)
/USART3_RX_PU: R29.2, U1.52 (PC11)
/USB_CC1: D4.1, J1.A5 (CC1), R1.1, R52.1
/USB_CC1_ADC: R52.2, U1.14 (PA0)
/USB_CC2: D4.2, J1.B5 (CC2), R2.1, R53.1
/USB_CC2_ADC: R53.2, U1.27 (PB1)
/USB_DM: J1.A7 (DN1), J1.B7 (DN2), U1.44 (PA11), U4.3 (I/O2), U4.4 (I/O2)
/USB_DP: J1.A6 (DP1), J1.B6 (DP2), U1.45 (PA12), U4.1 (I/O1), U4.6 (I/O1)
/VBAT: C5.1, Q1.3 (D), Q6.2 (S), Q8.2 (S), R20.2, R32.1, U2.5 (BAT)
/VBAT_ADC: C18.1, R21.2, R22.1, U1.16 (PA2)
/VBAT_CONN: F2.1, J3.1
/VBAT_FUSED: F2.2, Q6.3 (D), Q11.2 (S)
/VBAT_RP_CLAMP: Q11.3 (D), R30.1
/VBAT_RP_EN: Q7.1 (G), R30.2, R31.1
/VBAT_RP_G: Q6.1 (G), Q7.3 (D), R20.1
/VBAT_SNS_G: Q8.1 (G), Q9.3 (D), R32.2
/VBAT_SW: Q8.3 (D), R21.1
/VBUS: C4.1, C23.1, D1.2 (+), D3.2 (K), F1.2, Q1.1 (G), R4.1, R23.1, U2.4 (VCC), U4.5 (VBUS)
/VBUS_IN: C3.1, F1.1, J1.A4B9 (VBUS), J1.B4A9 (VBUS)
/VBUS_SNS: R23.2, R24.1, U1.42 (PA9)
/VBUS_WAKE_G: C23.2, Q5.1 (G), R50.1
/VCAP1: C10.1, U1.30 (VCAP_1)
/VDDA: C21.1, C22.1, L2.2, U1.13 (VDDA/VREF+)
/VSYS: C6.1, C9.1, C20.2, D1.1 (-), J2.12, Q1.2 (S), Q3.2 (S), R17.1, R31.2, U3.5 (VIN), U3.8 (VINA)

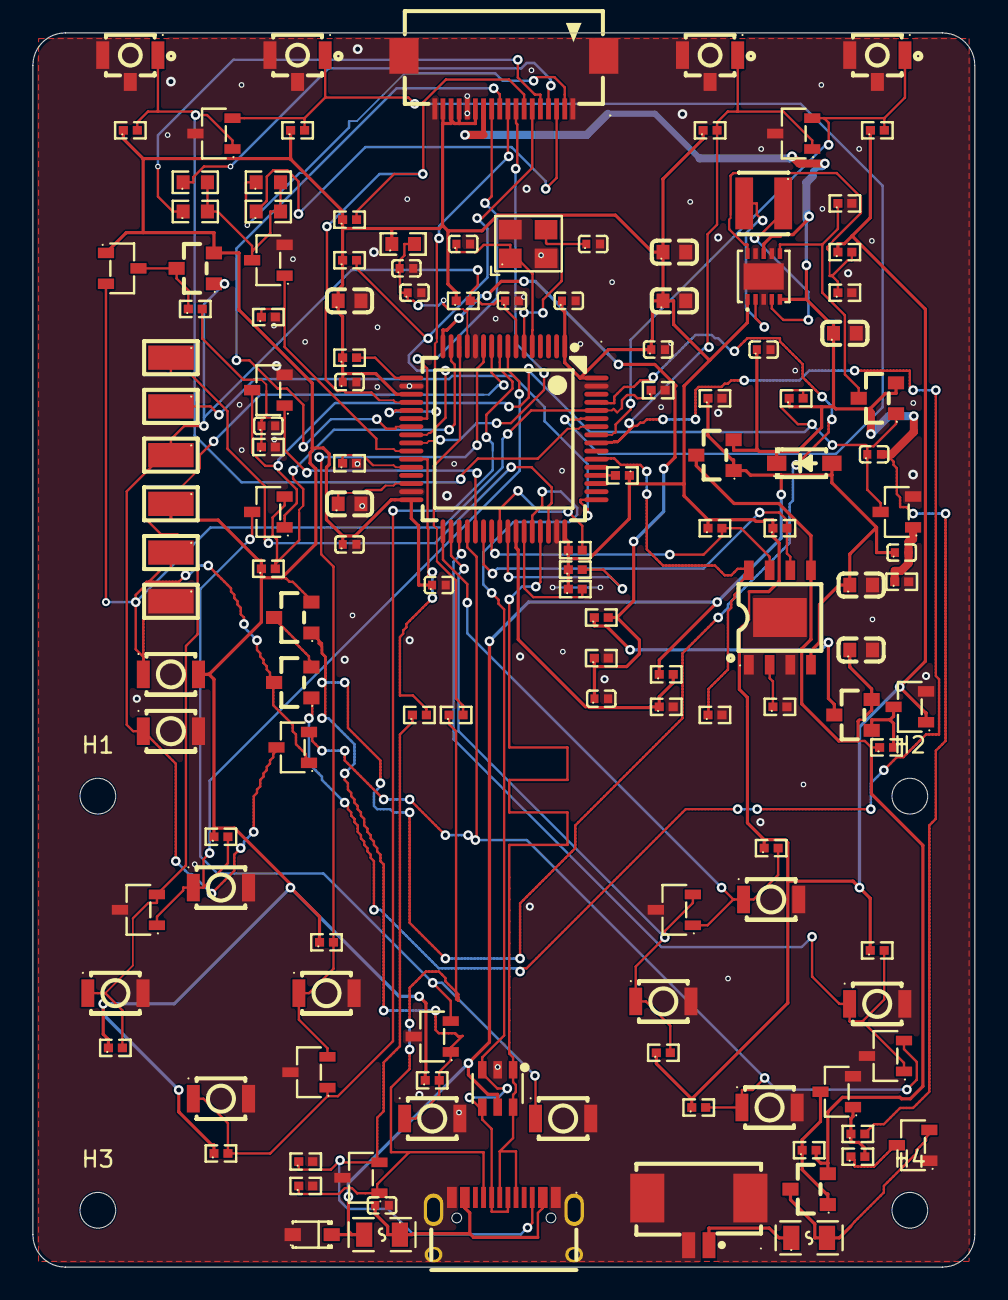
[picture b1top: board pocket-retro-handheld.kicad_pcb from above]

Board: 2 copper layers, 58.0 x 76.0 mm, 140 parts (0 on the bottom side), 75 nets.

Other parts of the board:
H1, H2, H3, H4: MountingHole_2.2mm_M2

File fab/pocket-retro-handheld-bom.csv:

Comment,Designator,Footprint,LCSC Part #
12pF,"C1,C2",C0402,C1547
4.7uF,"C4,C6,C10,C16",C0603,C19666
100nF,"C3,C8,C9,C11,C12,C13,C14,C18,C20,C21",C0402,C307331
1uF,"C15,C19,C22,C23",C0402,C29266
10uF,"C5,C7,C17",C0603,C380317
B5819W SL,D1,SOD-123_L2.7-W1.6-LS3.7-RD-1,C8598
PESD5V0S2BT,"D4,D6,D7,D8,D9,D10,D11,D12",SOT-23-3_L2.9-W1.3-P0.95-LS2.4-BR,C2687130
BAT54C,"D2,D5",SOT-23-3_L2.9-W1.3-P1.90-LS2.4-BR,C916424
SD05,D3,SOD-323_L1.8-W1.3-LS2.5-FD,C502527
BSMD0805-110-12V,"F1,F2",F0805,C910824
TYPE-C-31-M-12,J1,USB-C_SMD-TYPE-C-31-M-12_1,C165948
FH12-18S-0.5SH(55),J2,FPC-SMD_FH12-18S-0.5SH-55,C506792
532610271,J3,CONN-SMD_532610271,C177225
2.2uH,L1,IND-SMD_L3.0-W3.0,C43389
BLM18PG121SN1D,L2,L0603,C14709
AO3401A,"Q1,Q3,Q6,Q8,Q10,Q12,Q13",SOT-23_L2.9-W1.3-P1.90-LS2.4-BR,C15127
AO3400A,"Q2,Q4,Q5,Q7,Q9,Q11,Q14",SOT-23-3_L2.9-W1.3-P1.90-LS2.4-BR,C20917
5.1k,"R1,R2,R4,R23",R0402,C25905
100k,"R6,R10,R16,R17,R20,R31,R32,R49,R51",R0402,C25741
10k,"R7,R8,R11,R12,R13,R14,R15,R19,R21,R22,R24,R25,R26,R27,R28,R29,R30,R33,R34,R35,R36,R37,R38,R39,R40,R41,R42,R43,R44,R45,R52,R53",R0402,C25744
560k,"R5,R18,R50",R0402,C132339
3.3k,R3,R0402,C25890
100,"R9,R46,R47,R48",R0603,C22775
B3U-1000P,"SW1,SW2,SW3,SW4,SW5,SW6,SW7,SW8,SW9,SW10,SW15,SW16",KEY-SMD_B3U-1000PM,C231329
B3U-3100P,"SW11,SW12,SW13,SW14",SW-SMD_3P-L3.0-W2.5-LS4.0,C6748648
STM32F412RET6,U1,LQFP-64_L10.0-W10.0-P0.50-LS12.0-BL,C89374
TP4056,U2,ESOP-8_L4.9-W3.9-P1.27-LS6.0-BL-EP,C725790
RT6150AGQW,U3,WDFN-10_L3.0-W3.0-P0.50-BL-EP,C147971
USBLC6-2SC6,U4,SOT-23-6_L2.9-W1.6-P0.95-LS2.8-BL,C2687116
TXM12M0004322CBCDO00T,Y1,OSC-SMD_4P-L3.2-W2.5-BL,C362368
